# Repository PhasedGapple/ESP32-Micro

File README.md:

# ESP32-Micro
An ESP32-S3 which focuses on being a little long but really thin.
# Downloader Wiring
Top/Bigger Pin Header: Left to right from USB C 4PIN Receptor: GND, D+, D-, VBUS
Bottom: Replace with Pin Socket, my KiCad knowledge limitations made it show a Pin Header
# Dimensions
ESP32: 15x44 \
Downloader: 20x13
# Differences between the normal ESP32-S3 vs ESP32 Micro
- No built-in LEDs
- Very poor wifi range because the board doesnt have an antenna. You can put a metal wire on the antenna pin before soldering if you really want wifi or bluetooth.
- No VIN pins so if you want to power it thru 5v use the downloader module.
- Attachable USB C board so if you dont need USB-C then you can save the space by not using it.

# Images

# Info
Thank you a lot from Fabricate - Hack Club, I really appreciate you and it helping me and other poeple fund this project, this project is something I really need for my other projects

I used AI to research stuff like what parts I would need and some other stuff. I verify everything I'm not sure of.

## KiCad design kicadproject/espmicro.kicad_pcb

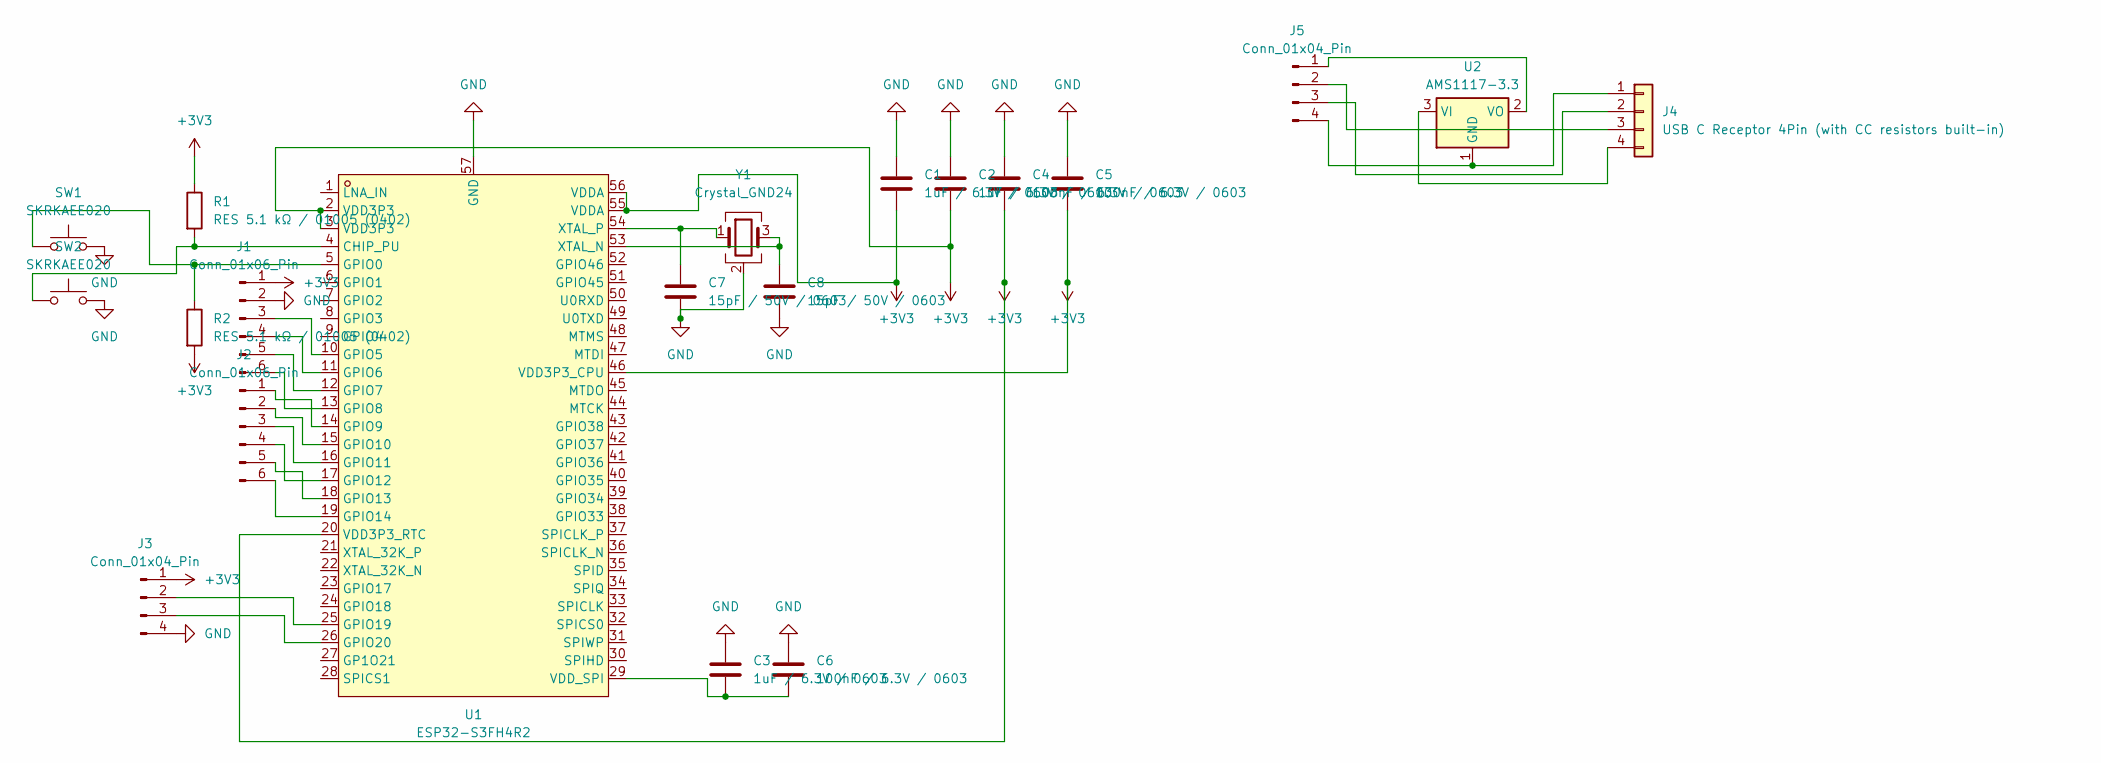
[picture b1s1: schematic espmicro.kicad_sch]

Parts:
C1, C2, C3: 1uF / 6.3V / 0603; C_0603_1608Metric_Pad1.08x0.95mm_HandSolder
C4, C5, C6: 100nF / 6.3V / 0603; C_0603_1608Metric_Pad1.08x0.95mm_HandSolder
C7, C8: 15pF / 50V / 0603; C_0603_1608Metric_Pad1.08x0.95mm_HandSolder
J1, J2: Conn_01x06_Pin; PinHeader_1x06_P2.00mm_Vertical
J3, J5: Conn_01x04_Pin; PinHeader_1x04_P2.00mm_Vertical
J4: USB C Receptor 4Pin (with CC resistors built-in); PinHeader_1x04_P2.54mm_Vertical
R1, R2: RES 5.1 kΩ / 01005 (0402); C_01005_0402Metric_Pad0.57x0.30mm_HandSolder
SW1, SW2: SKRKAEE020; SW_Push_SPST_NO_Alps_SKRK
U1: ESP32-S3FH4R2; QFN-56_L7.0-W7.0-P0.40-BL-EP5.7; MPN ESP32-S3FH4R2; LCSC Part C3013940
U2: AMS1117-3.3; SOT-223-3_TabPin2
Y1: Crystal_GND24; Crystal_SMD_0603-4Pin_6.0x3.5mm_HandSoldering

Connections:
+3V3: C1.2, C2.2, C4.2, C5.2, J1.1, J3.1, R1.1, R2.2, U1.2 (VDD3P3), U1.3 (VDD3P3), U1.20 (VDD3P3_RTC), U1.46 (VDD3P3_CPU), U1.55 (VDDA), U1.56 (VDDA)
GND: C1.1, C2.1, C3.1, C4.1, C5.1, C6.1, C7.2, C8.2, J1.2, J3.4, SW1.2, SW2.2, U1.57 (GND), Y1.2 (G), Y1.4 (G)
unnamed: J1.3, U1.10 (GPIO5)
unnamed: J1.4, U1.11 (GPIO6)
unnamed: J1.5, U1.12 (GPIO7)
unnamed: J1.6, U1.13 (GPIO8)
unnamed: J2.1, U1.14 (GPIO9)
unnamed: J2.2, U1.15 (GPIO10)
unnamed: J2.3, U1.16 (GPIO11)
unnamed: J2.4, U1.17 (GPIO12)
unnamed: J2.5, U1.18 (GPIO13)
unnamed: J2.6, U1.19 (GPIO14)
unnamed: J3.2, U1.25 (GPIO19)
unnamed: J3.3, U1.26 (GPIO20)
unnamed: J4.1, J5.4, U2.1 (GND)
unnamed: J4.2, J5.3
unnamed: J4.3, J5.2
unnamed: J4.4, U2.3 (VI)
unnamed: J5.1, U2.2 (VO)
unnamed: R1.2, SW2.1, U1.4 (CHIP_PU)
unnamed: R2.1, SW1.1, U1.5 (GPIO0)
unnamed: C3.2, C6.2, U1.29 (VDD_SPI)
unnamed: C8.1, U1.53 (XTAL_N), Y1.3
unnamed: C7.1, U1.54 (XTAL_P), Y1.1

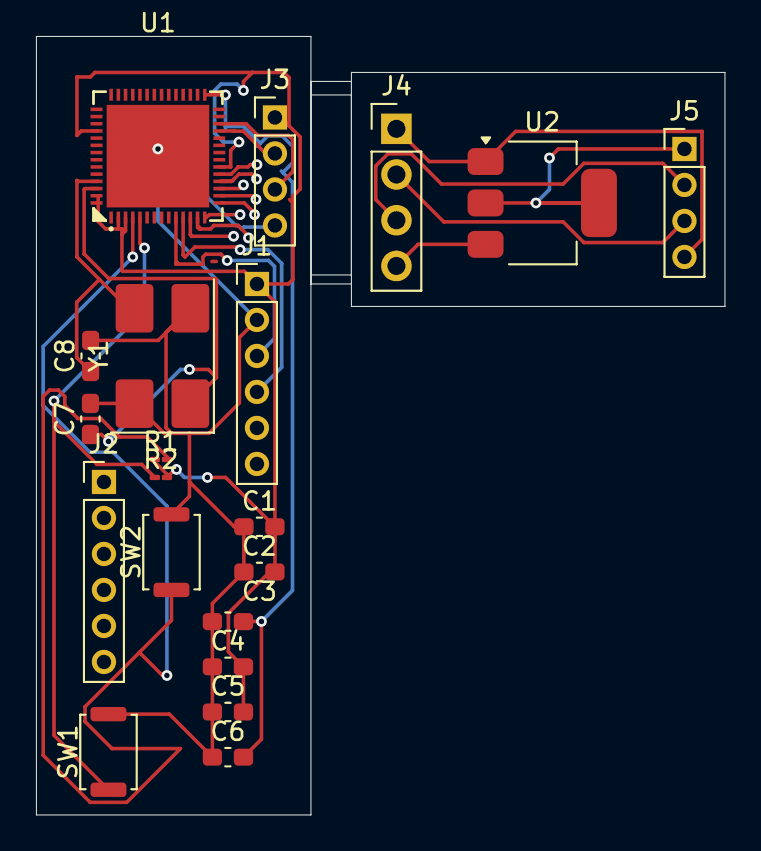
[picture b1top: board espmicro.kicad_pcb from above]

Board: 4 copper layers, 38.2 x 43.2 mm, 20 parts (0 on the bottom side), 24 nets.
